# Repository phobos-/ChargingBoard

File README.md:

# ChargingBoard
## 1S JST-PH 2.0 series-parallel charging board

This board can balance-charge from 6 to 30 1s lipos. 

## 2S XT30 series-parallel charging board

This board can balance-charge from 3 to 12 2s lipos. 

## How it works

The charger will see the board as a 6s battery. To complete the board you need a balance plug for 6s, an XT60 female connector (or any other connector that fits your charger), 12 XT30 (XT30U) or 30 JST-PH 2.0 standard male connectors and some wire. Make sure to order in 2oz copper for maximum performance.

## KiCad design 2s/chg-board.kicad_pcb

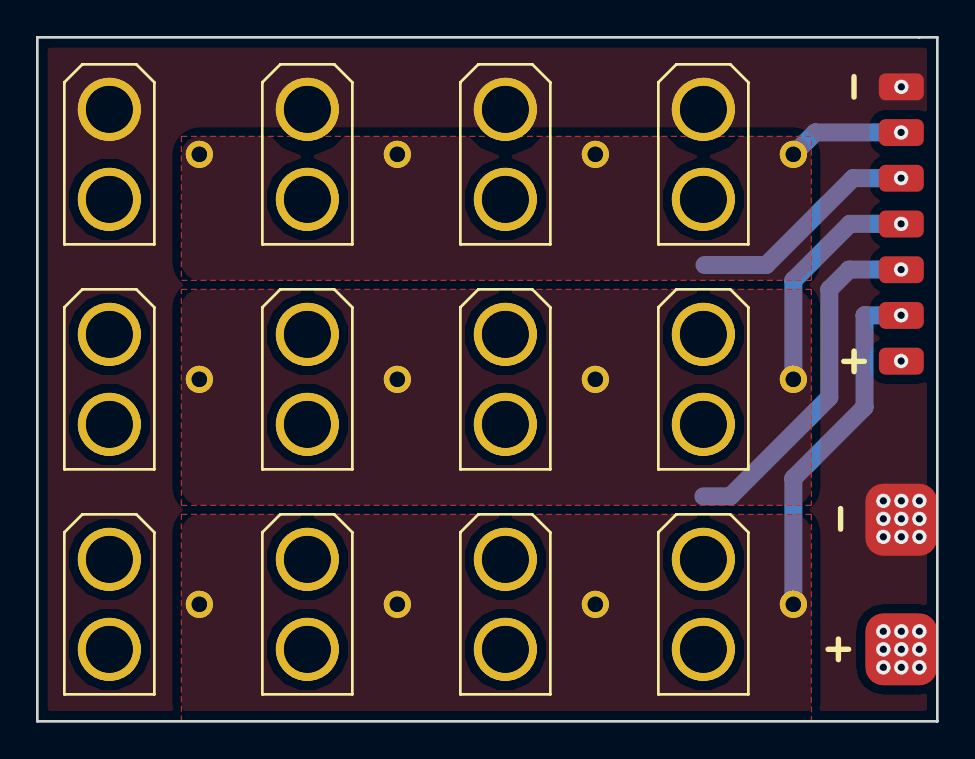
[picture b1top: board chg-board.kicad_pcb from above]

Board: 2 copper layers, 50.0 x 38.0 mm, 6 parts (0 on the bottom side), 7 nets.

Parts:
J1, J2, J3, J4: Conn_01x09_Male; xt30_3
J5: Conn_01x02_Female; xt60_pad
J6: Conn_01x07_Female; balance_plug

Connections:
GND: J1.9, J2.9, J3.9, J4.9, J5.2, J6.7
unnamed: J1.2, J2.2, J3.2, J4.2, J6.2
unnamed: J1.3, J1.4, J2.3, J2.4, J3.3, J3.4, J4.3, J4.4, J6.3
unnamed: J1.5, J2.5, J3.5, J4.5, J6.4
unnamed: J1.6, J1.7, J2.6, J2.7, J3.6, J3.7, J4.6, J4.7, J6.5
unnamed: J1.8, J2.8, J3.8, J4.8, J6.6
VCC: J1.1, J2.1, J3.1, J4.1, J5.1, J6.1

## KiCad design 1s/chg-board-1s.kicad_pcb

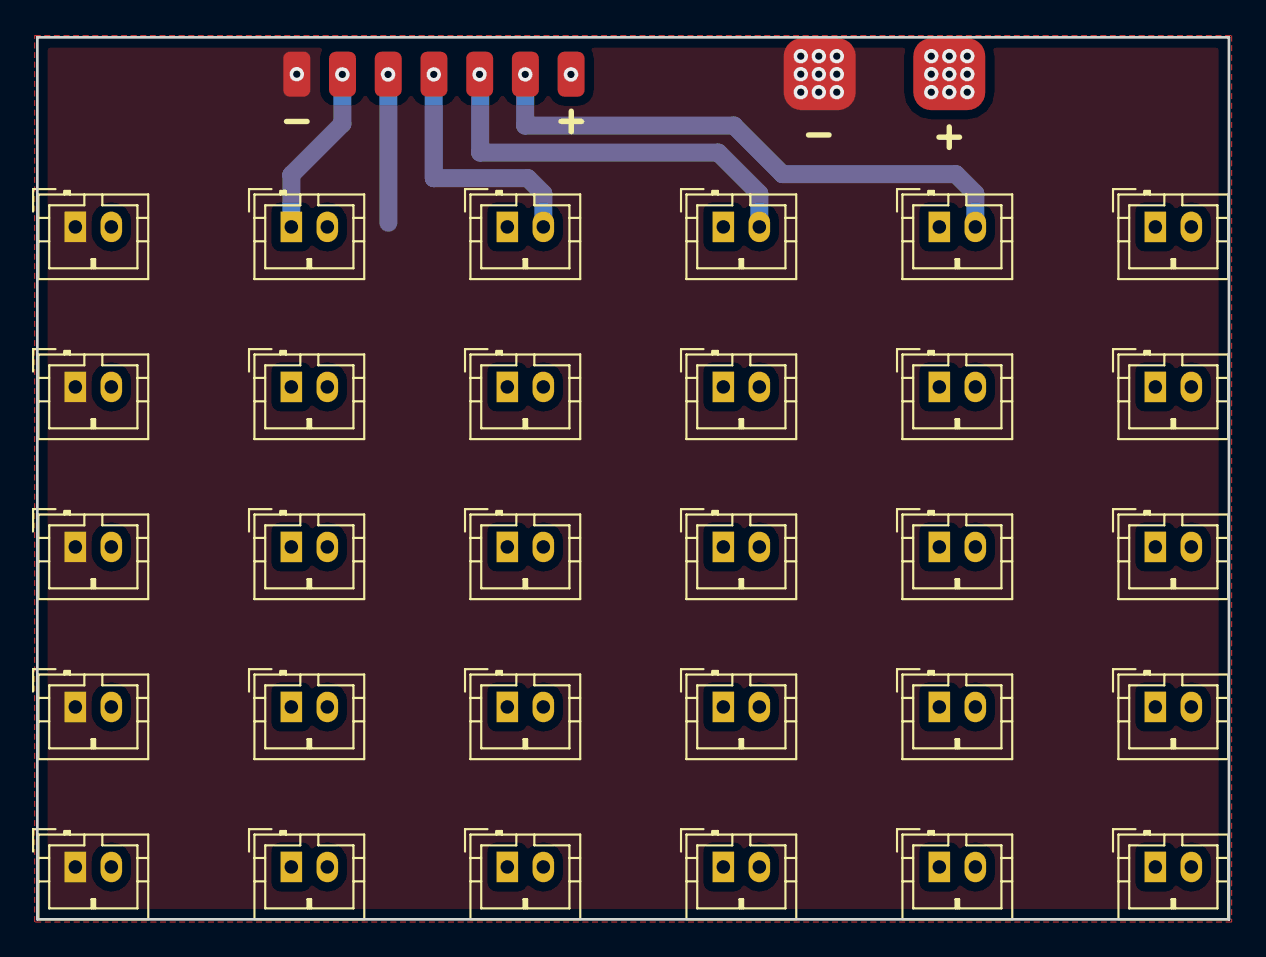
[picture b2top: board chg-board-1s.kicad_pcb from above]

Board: 2 copper layers, 66.2 x 49.0 mm, 7 parts (0 on the bottom side), 7 nets.

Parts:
J1, J2, J3, J4, J7: Conn_01x12_Male; ph2.0_6
J5: Conn_01x02_Female; xt60_pad
J6: Conn_01x07_Female; balance_plug

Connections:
GND: J1.1, J2.1, J3.1, J4.1, J5.2, J6.7, J7.1
unnamed: J1.2, J1.3, J2.2, J2.3, J3.2, J3.3, J4.2, J4.3, J6.6, J7.2, J7.3
unnamed: J1.4, J1.5, J2.4, J2.5, J3.4, J3.5, J4.4, J4.5, J6.5, J7.4, J7.5
unnamed: J1.6, J1.7, J2.6, J2.7, J3.6, J3.7, J4.6, J4.7, J6.4, J7.6, J7.7
unnamed: J1.8, J1.9, J2.8, J2.9, J3.8, J3.9, J4.8, J4.9, J6.3, J7.8, J7.9
unnamed: J1.10, J1.11, J2.10, J2.11, J3.10, J3.11, J4.10, J4.11, J6.2, J7.10, J7.11
VCC: J1.12, J2.12, J3.12, J4.12, J5.1, J6.1, J7.12

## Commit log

2018-09-29 Added kicad files
2018-09-29 Flipped GND and VCC markings to better fit ISDT SC-608
2019-03-02 Added 1s variant, fixed xt30 footprint
2019-03-07 Some changes to 2s board
